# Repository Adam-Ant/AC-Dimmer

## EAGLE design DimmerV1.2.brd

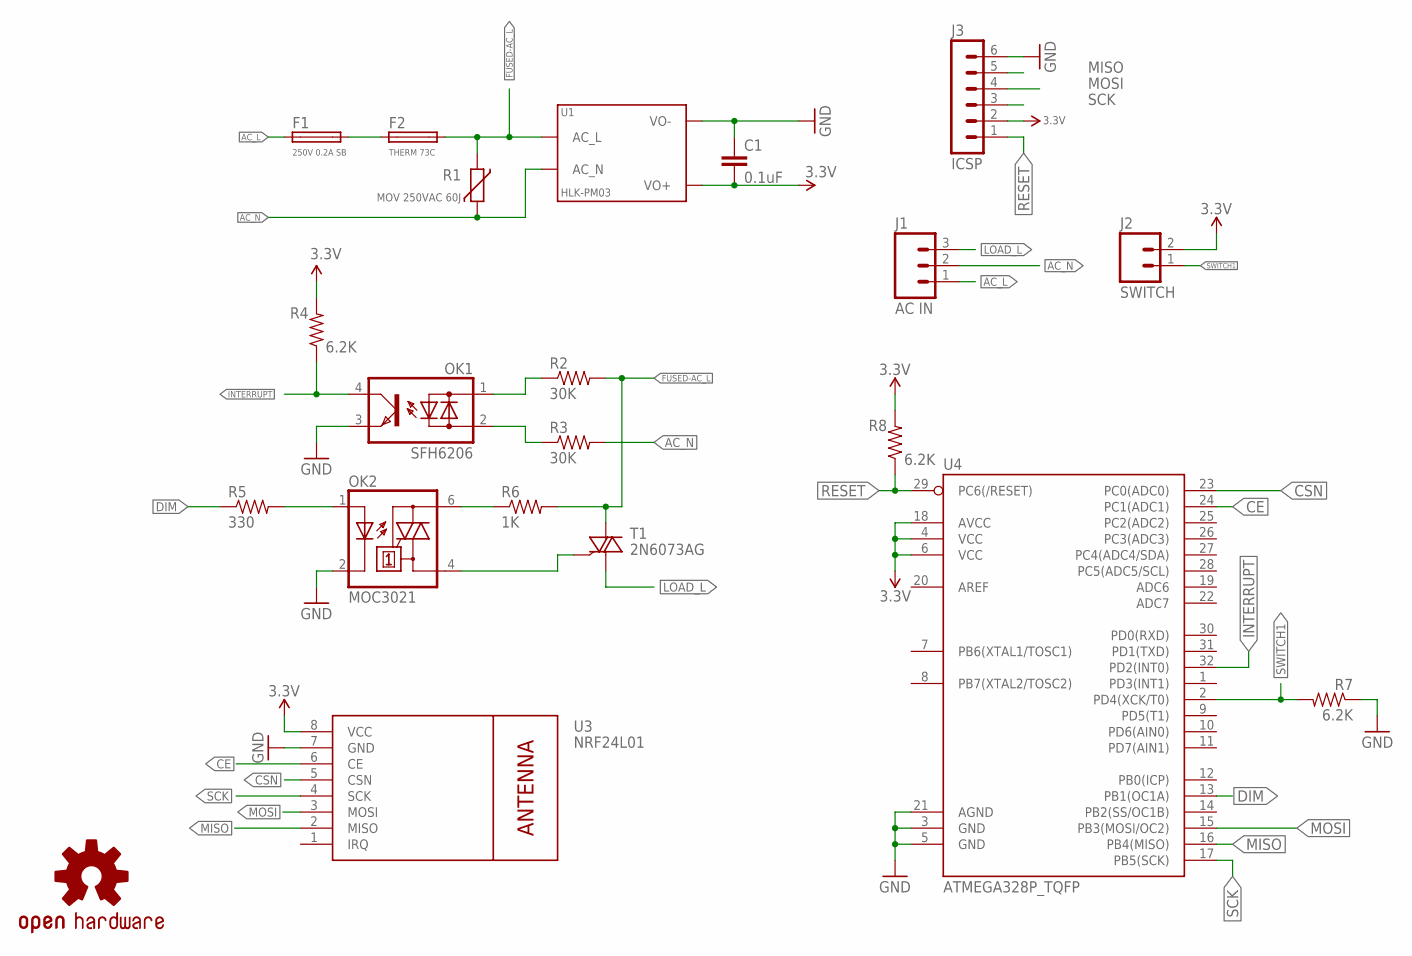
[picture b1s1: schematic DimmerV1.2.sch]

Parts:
C1: 0.1uF; 0805
F1: 250V 0.2A SB; TR5
F2: THERM 73C; TE5
J1: AC IN; SCREWTERMINAL-5MM-3
J2: SWITCH; SCREWTERMINAL-5MM-2
J3: ICSP; 06X1-PTH
LOGO1: OSHW-LOGOM; OSHW-LOGO-M
OK1: SFH6206; DIL4-SMD
OK2: MOC3021; DIL6-SMD
R1: MOV 250VAC 60J; S05K11
R2, R3: 30K; 0805
R4, R7, R8: 6.2K; 0805
R5: 330; 0805
R6: 1K; 0805
T1: 2N6073AG; TO220DS
U1: HLK-PM03
U3: NRF24L01; WIRELESS-NRF24L01-SMD
U4: ATMEGA328P_TQFP; TQFP32-08

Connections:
3.3V: C1.2, J2.2, J3.2, R4.2, R8.2, U1.VO+, U3.8 (VCC), U4.4 (VCC), U4.6 (VCC), U4.18 (AVCC)
AC_L: F1.1, J1.1
AC_N: J1.2, R1.2, R3.2, U1.AC_N
CE: U3.6 (CE), U4.24 (PC1(ADC1))
CSN: U3.5 (CSN), U4.23 (PC0(ADC0))
DIM: R5.1, U4.13 (PB1(OC1A))
FUSED-AC_L: F2.2, R1.1, R2.2, R6.2, T1.A2, U1.AC_L
GND: C1.1, J3.6, OK1.3 (E), OK2.2 (C), R7.1, U1.VO-, U3.7 (GND), U4.3 (GND), U4.5 (GND), U4.21 (AGND)
INTERRUPT: OK1.4 (C), R4.1, U4.32 (PD2(INT0))
LOAD_L: J1.3, T1.A1
MISO: J3.5, U3.2 (MISO), U4.16 (PB4(MISO))
MOSI: J3.4, U3.3 (MOSI), U4.15 (PB3(MOSI/OC2))
unnamed: F1.2, F2.1
unnamed: OK1.1 (AC1), R2.1
unnamed: OK1.2 (AC2), R3.1
unnamed: OK2.1 (A), R5.2
unnamed: OK2.4 (A1), T1.G
unnamed: OK2.6 (A2), R6.1
RESET: J3.1, R8.1, U4.29 (PC6(/RESET))
SCK: J3.3, U3.4 (SCK), U4.17 (PB5(SCK))
SWITCH1: J2.1, R7.2, U4.2 (PD4(XCK/T0))

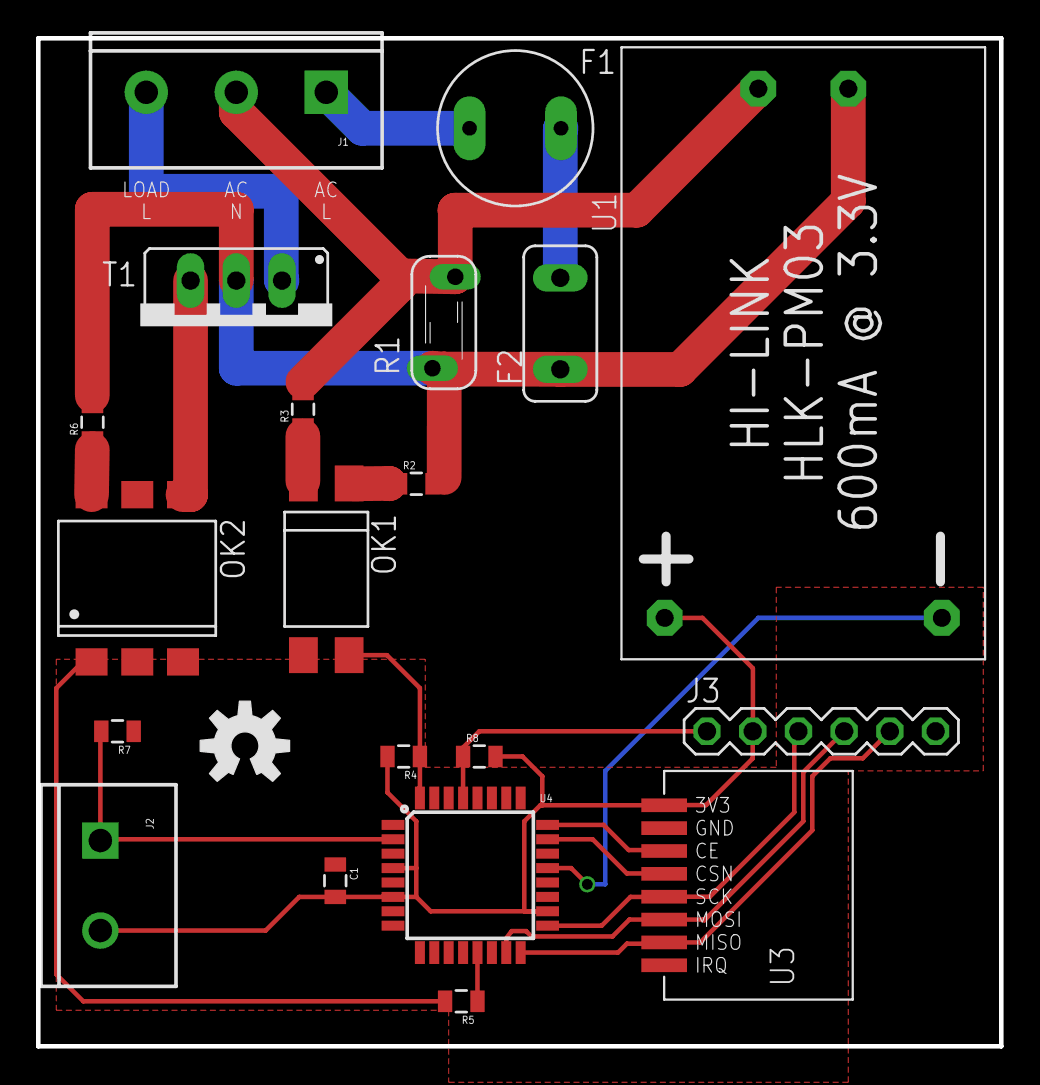
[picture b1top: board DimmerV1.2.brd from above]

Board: 2 copper layers, 53.5 x 56.0 mm, 21 parts (0 on the bottom side), 21 nets.

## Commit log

2016-08-04 Board layout fixes (C1)

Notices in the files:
parts and their libraries:
SparkFun-Capacitors: Licensing: Creative Commons ShareAlike 4.0 International - https://creativecommons.org/licenses/by-sa/4.0
